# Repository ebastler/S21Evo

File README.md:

# S21Evo
NOTE: This project is still WIP. An older revision is currently being prototyped and has served as a software development platform. The state published in this repository includes a variety of bugfixes and improvements over this version, but is as of now UNTESTED. The current firmware does not support these changes yet. Please do not order PCBs based off this repository (and if you do, don't complain about problems).

## Introduction
This project was born from the fact that the Convoy S21E is - in my opinion - one of the best budget flashlights out there. It is fairly compact for a 21700 class flashlight. 21700 batteries are a great compromise between size and capacity. It can fit a variety of emitters and optics. It is available in a lot of nice colors - and all that while being very affordable. I do, however, not like Convoys E-Switch drivers much due to some UI choices that do not reflect my preference. I also wanted faster charging and powerbank functionality included.

## Features
The S21Evo BST driver is a high-efficiency 6V 5A boost driver. It is based on the popular MPS MP3432 boost chip. Two shunts (1 Ohm and 7 mOhm) allow for a wide dynamic range (~100uA to 5A). The battery management (15W charging, 15W reverse powerbank functionality with proper USB-C handshake) is handled by a MPS MP2722. A STM32C072GBU controls both chips and can be programmed seamlessly via the built-in USB port of the flashlight. Thermal protection, low-voltage protection as well as reverse polarity protection are built in. RGB Aux (2 brightness levels per color) is available.

Some features I wanted to add (buck-boost supply for the MCU to allow for wider input voltage range, full 8bit RGB Aux, a MCU with built-in DAC instead of low-pass-filtered PWM) sadly had to be omitted due to severe space constraints in the S21E body. Fitting a USB-C port, battery spring, 2 DC-DC converters (15W and 30W) with as much filter capacity as possible as well as a QFN MCU in the given space was already a difficult task.

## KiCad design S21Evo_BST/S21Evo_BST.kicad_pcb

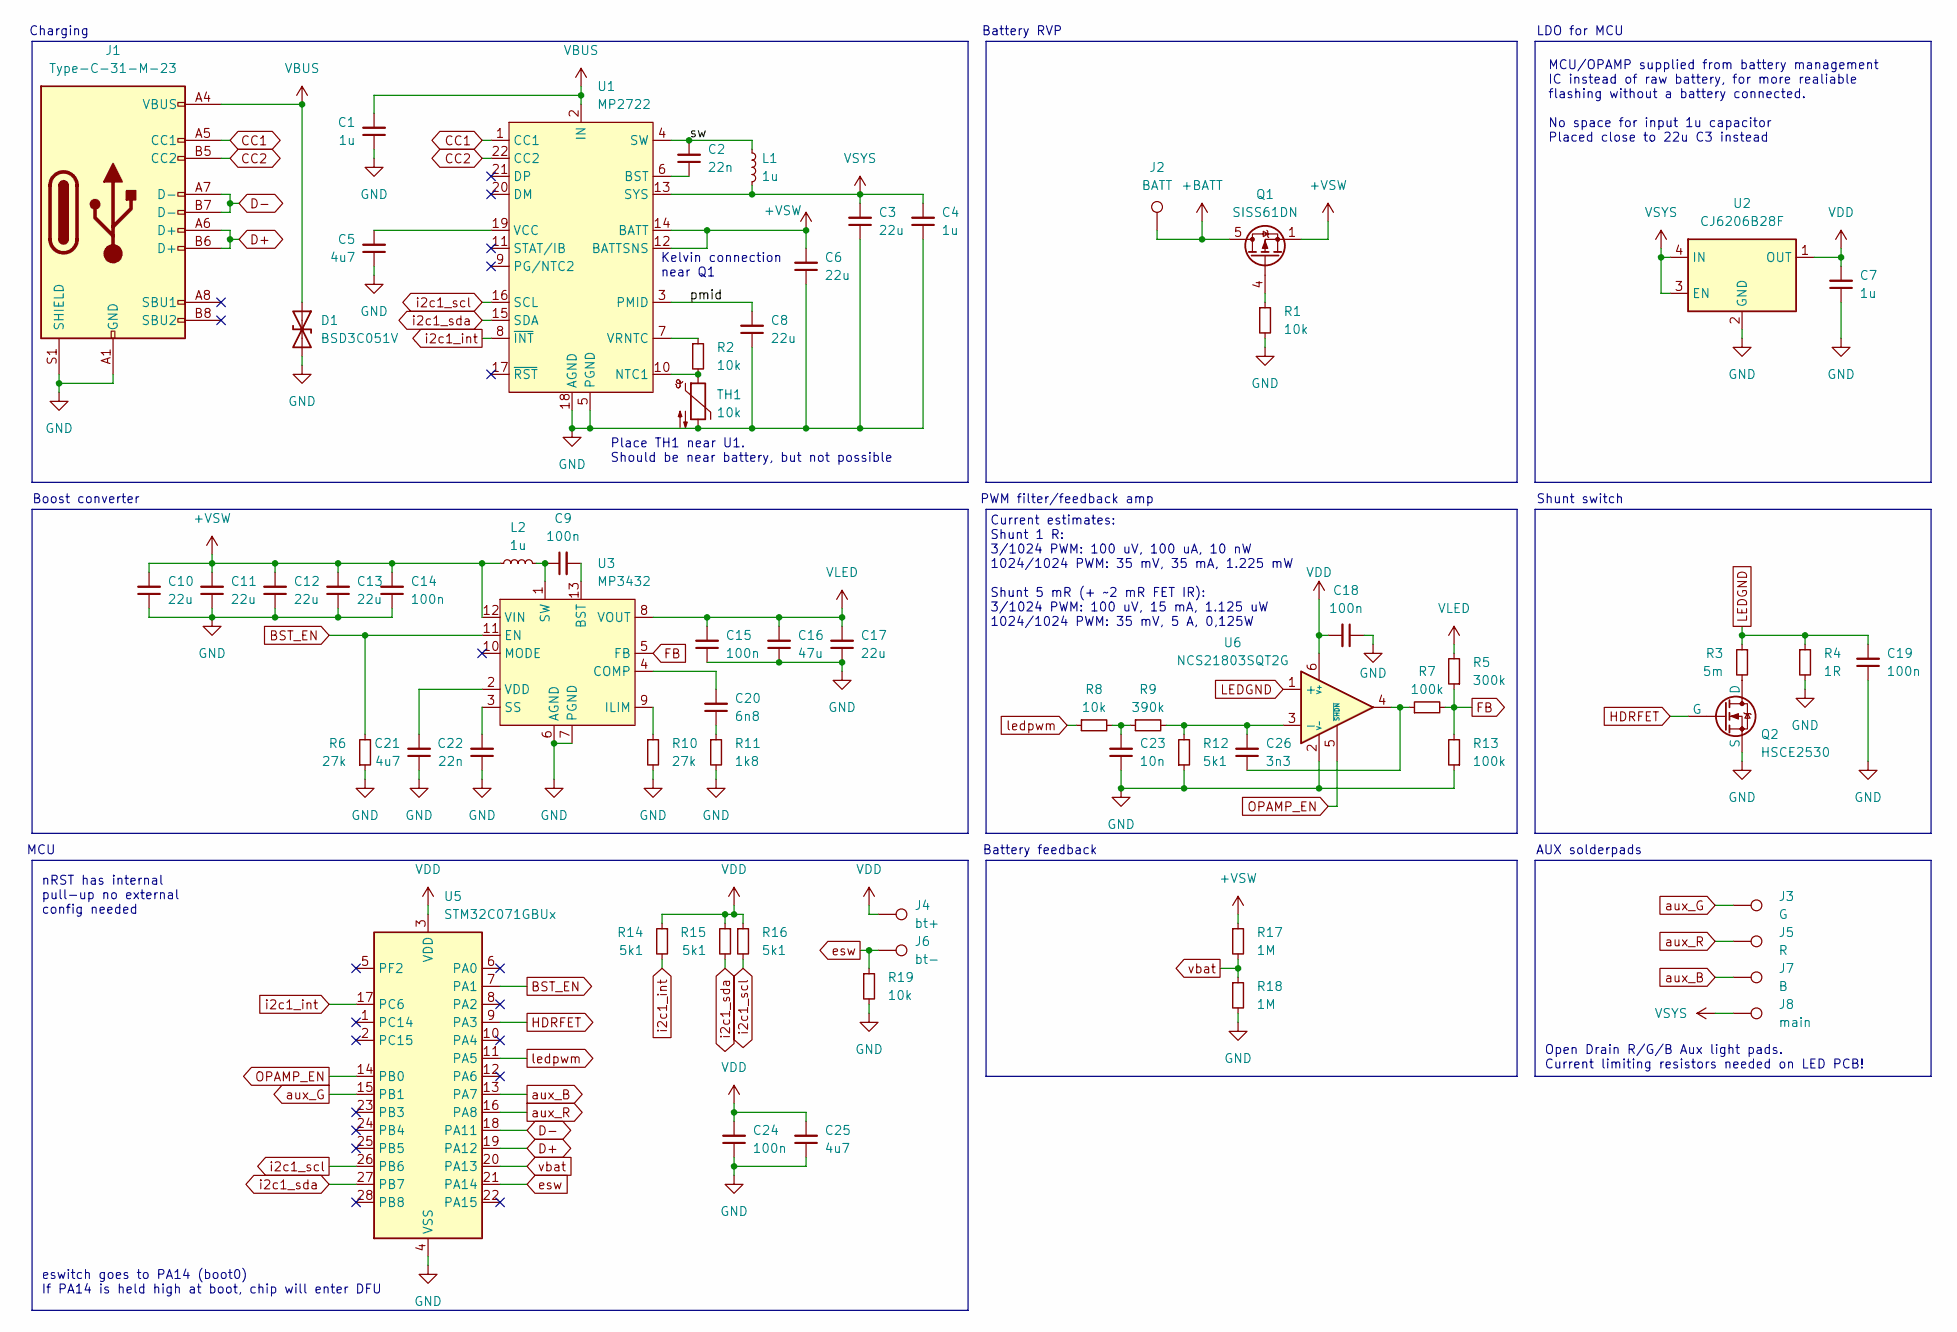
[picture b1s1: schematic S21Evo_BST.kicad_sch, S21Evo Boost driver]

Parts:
C1, C4, C7: 1u; C_0402_1005Metric; Part number CL05A105KA5NQNC; LCSC C52923
C2, C22: 22n; C_0402_1005Metric; Part number CL05B223KA5NNNC; LCSC C318578
C3, C6, C8, C10, C11, C13, C17: 22u; C_0603_1608Metric; Part number CL10A226MO7JZNC; LCSC C2762594
C5, C21, C25: 4u7; C_0402_1005Metric; Part number CL05A475MP5NRNC; LCSC C23733
C9, C14, C15, C18, C19, C24: 100n; C_0402_1005Metric; Part number CL05B104KB54PNC; LCSC C307331
C12: 22u; C_0805_2012Metric; Part number CL21A226MAQNNNE; LCSC C45783
C16: 47u; C_1206_3216Metric; Part number CL31A476MPHNNNE; LCSC C96123
C20: 6n8; C_0402_1005Metric; Part number CL05B682KB5NNNC; LCSC C318580
C23: 10n; C_0402_1005Metric; Part number CL05B103KB5NNNC; LCSC C15195
C26: 3n3; C_0402_1005Metric; Part number CL05B332KB5NNNC; LCSC C26404
D1: BSD3C051V; D_SOD-323; Part number BSD3C051V; LCSC C151996
J1: Type-C-31-M-23; USB_C_Receptacle_HRO_TYPE-C-31-M-23; Part number TYPE-C-31-M-23; LCSC C530613
J2: BATT; spring_6mm
J3: G; auxpad
J4: bt+; auxpad
J5: R; auxpad
J6: bt-; auxpad
J7: B; auxpad
J8: main; auxpad
L1: 1u; L_Changjiang_FTC322520S; Part number YSMC322520H-1R0MB; LCSC C46962057
L2: 1u; L_Bourns_SRP6060FA; Part number YSPIT0660A-1R0M; LCSC C18199443
Q1: SISS61DN; Vishay_PowerPAK_1212-8_Single; Part number SISS61DN-T1-GE3; LCSC C3289430
Q2: HSCE2530; Vishay_PowerPAK_1212-8_Single; Part number HSCE2530; LCSC C701041
R1, R2, R8, R19: 10k; R_0402_1005Metric; Part number 0402WGF1002TCE; LCSC C25744
R3: 5m; R_0805_2012Metric; Part number MS05W2F500NT5E; LCSC C92742
R4: 1R; R_0402_1005Metric; Part number 0402WGF100KTCE; LCSC C25086
R5: 300k; R_0402_1005Metric; Part number 0402WGF3003TCE; LCSC C25774
R6, R10: 27k; R_0402_1005Metric; Part number 0402WGF2702TCE; LCSC C25771
R7, R13: 100k; R_0402_1005Metric; Part number 0402WGF1003TCE; LCSC C25741
R9: 390k; R_0402_1005Metric; Part number 0402WGF3903TCE; LCSC C25782
R11: 1k8; R_0402_1005Metric; Part number 0402WGF1801TCE; LCSC C25871
R12, R14, R15, R16: 5k1; R_0402_1005Metric; Part number 0402WGF5101TCE; LCSC C25905
R17, R18: 1M; R_0402_1005Metric; Part number 0402WGF1004TCE; LCSC C26083
TH1: 10k; R_0402_1005Metric; Part number NTCG103JF103FT1; LCSC C209959
U1: MP2722; QFN-22_MP2722_2.5x3.5mm_P0.4mm; Part number MP2722GRH-0000-Z; LCSC C20099551
U2: CJ6206B28F; OnSemi_XDFN4-1EP_1.0x1.0mm_EP0.52x0.52mm; Part number CJ6206B28F; LCSC C2829371
U3: MP3432; QFN-13_3x4mm_P0.5mm; Part number MP3432GL-Z; LCSC C3187976
U5: STM32C071GBUx; QFN-28_4x4mm_P0.5mm; Part number STM32C071GBU6; LCSC C42113261
U6: NCS21803SQT2G; SOT-363_SC-70-6; Part number NCS21803SQT2G; LCSC C5209288

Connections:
+BATT: J2.1 (1_1), Q1.5 (D)
+VSW: C6.2, C10.2, C11.2, C12.2, C13.2, C14.2, L2.1, Q1.1 (S), Q1.2 (S), Q1.3 (S), R17.1, U1.12 (BATTSNS), U1.14 (BATT), U3.12 (VIN)
/pmid: C8.2, U1.3 (PMID)
/sw: C2.2, L1.1, U1.4 (SW)
BST_EN: R6.2, U3.11 (EN), U5.7 (PA1)
CC1: J1.A5 (CC1), U1.1 (CC1)
CC2: J1.B5 (CC2), U1.22 (CC2)
D+: J1.A6 (D+), J1.B6 (D+), U5.19 (PA12)
D-: J1.A7 (D-), J1.B7 (D-), U5.18 (PA11)
FB: R5.1, R7.2, R13.2, U3.5 (FB)
GND: C1.1, C3.1, C4.1, C5.1, C6.1, C7.1, C8.1, C10.1, C11.1, C12.1, C13.1, C14.1, C15.1, C16.1, C17.1, C18.1, C19.1, C21.1, C22.1, C23.1, C24.1, C25.1, D1.2 (A2), J1.A1 (GND), J1.A12 (GND), J1.B1 (GND), J1.B12 (GND), J1.S1 (SHIELD), Q2.1 (S), Q2.2 (S), Q2.3 (S), R1.2, R4.2, R6.1, R10.2, R11.2, R12.1, R13.1, R18.2, R19.2, TH1.2, U1.5 (PGND), U1.18 (AGND), U2.2 (GND), U2.5 (GND), U3.6 (AGND), U3.7 (PGND), U5.4 (VSS), U6.2 (V-)
HDRFET: Q2.4 (G), U5.9 (PA3)
LEDGND: C19.2, R3.1, R4.1, U6.1 (+)
unnamed: C20.1, R11.1
unnamed: C23.2, R8.2, R9.1
unnamed: C26.1, R7.1, U6.4
unnamed: Q1.4 (G), R1.1
unnamed: Q2.5 (D), Q2.6 (D), Q2.7 (D), Q2.8 (D), Q2.9 (D), R3.2
unnamed: C2.1, U1.6 (BST)
unnamed: R2.2, TH1.1, U1.10 (NTC1)
unnamed: C5.2, U1.19 (VCC)
unnamed: R2.1, U1.7 (VRNTC)
unnamed: C9.2, U3.13 (BST)
unnamed: C20.2, U3.4 (COMP)
unnamed: R10.1, U3.9 (ILIM)
unnamed: C22.2, U3.3 (SS)
unnamed: C9.1, L2.2, U3.1 (SW)
unnamed: C21.2, U3.2 (VDD)
unnamed: C26.2, R9.2, R12.2, U6.3 (-)
OPAMP_EN: U5.14 (PB0), U6.5 (~SHDN)
VBUS: C1.2, D1.1 (A1), J1.A4 (VBUS), J1.A9 (VBUS), J1.B4 (VBUS), J1.B9 (VBUS), U1.2 (IN)
VDD: C7.2, C18.2, C24.2, C25.2, J4.1 (1_1), R14.1, R15.1, R16.1, U2.1 (OUT), U5.3 (VDD), U6.6 (V+)
VLED: C15.2, C16.2, C17.2, R5.2, U3.8 (VOUT)
VSYS: C3.2, C4.2, J8.1 (1_1), L1.2, U1.13 (SYS), U2.3 (EN), U2.4 (IN)
aux_B: J7.1 (1_1), U5.13 (PA7)
aux_G: J3.1 (1_1), U5.15 (PB1)
aux_R: J5.1 (1_1), U5.16 (PA8)
esw: J6.1 (1_1), R19.1, U5.21 (PA14)
i2c1_int: R14.2, U1.8 (~INT), U5.17 (PC6)
i2c1_scl: R16.2, U1.16 (SCL), U5.26 (PB6)
i2c1_sda: R15.2, U1.15 (SDA), U5.27 (PB7)
ledpwm: R8.1, U5.11 (PA5)
vbat: R17.2, R18.1, U5.20 (PA13)

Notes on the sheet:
eswitch goes to PA14 (boot0) If PA14 is held high at boot, chip will enter DFU
nRST has internal pull-up no external config needed
Place TH1 near U1. Should be near battery, but not possible
MCU/OPAMP supplied from battery management IC instead of raw battery, for more realiable flashing without a battery connected. No space for input 1u capacitor Placed close to 22u C3 instead
LDO for MCU
Battery feedback
PWM filter/feedback amp
Battery RVP
Shunt switch
Current estimates: Shunt 1 R: 3/1024 PWM: 100 uV, 100 uA, 10 nW 1024/1024 PWM: 35 mV, 35 mA, 1.225 mW Shunt 5 mR (+ ~2 mR FET IR): 3/1024 PWM: 100 uV, 15 mA, 1.125 uW 1024/1024 PWM: 35 mV, 5 A, 0,125W
Charging
MCU
AUX solderpads
Boost converter
Open Drain R/G/B Aux light pads. Current limiting resistors needed on LED PCB!
Kelvin connection near Q1

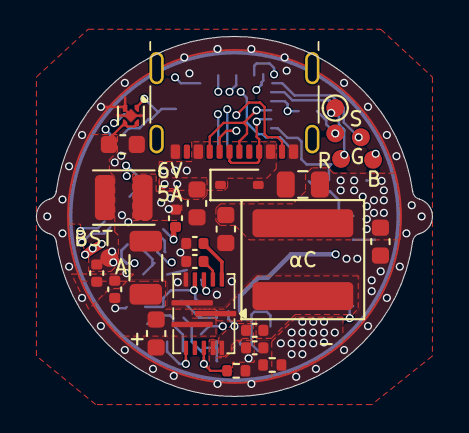
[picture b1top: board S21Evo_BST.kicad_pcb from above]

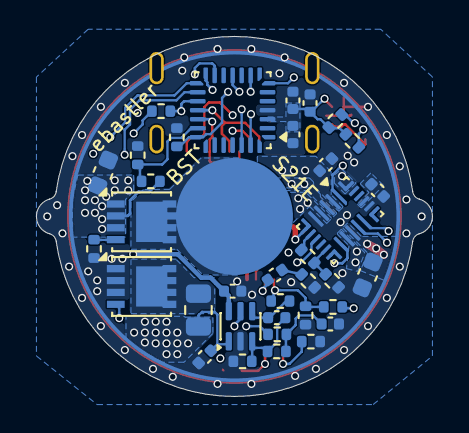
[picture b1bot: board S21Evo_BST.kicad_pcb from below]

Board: 4 copper layers, 22.0 x 20.0 mm, 64 parts (36 on the bottom side), 43 nets.

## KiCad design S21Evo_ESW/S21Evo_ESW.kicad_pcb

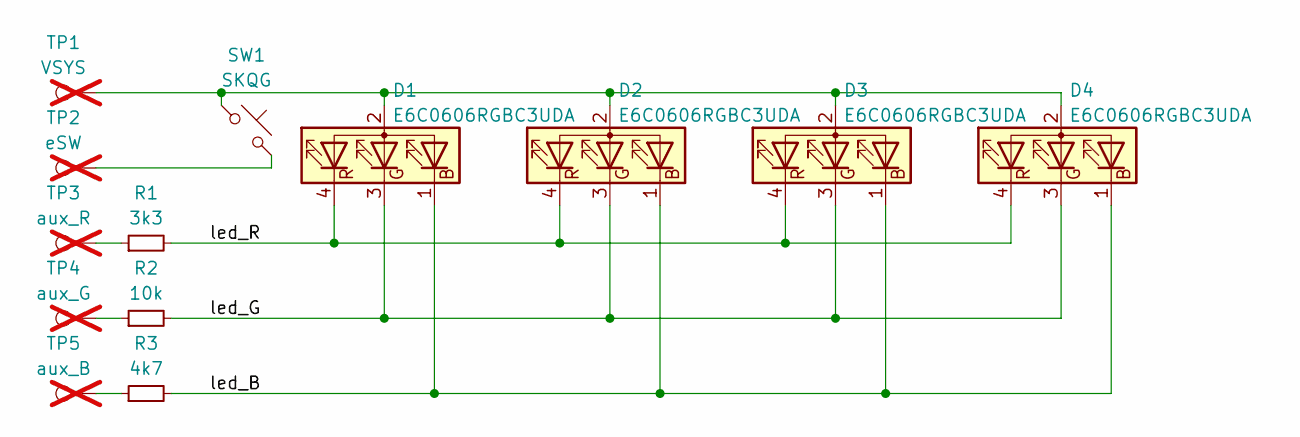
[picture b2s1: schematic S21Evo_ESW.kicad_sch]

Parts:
D1, D2, D3, D4: E6C0606RGBC3UDA; LED_1616; Part number E6C0606RGBC3UDA; LCSC C375569
R1: 3k3; R_0402_1005Metric; Part number 0402WGF3301TCE; LCSC C25890
R2: 10k; R_0402_1005Metric; Part number 0402WGF1002TCE; LCSC C25744
R3: 4k7; R_0402_1005Metric; Part number 0402WGF4701TCE; LCSC C25900
SW1: SKQG; SW_SPST_SKQG_WithStem; Part number SKQGABE010; LCSC C115351
TP1: VSYS; auxpad; not fitted
TP2: eSW; auxpad; not fitted
TP3: aux_R; auxpad; not fitted
TP4: aux_G; auxpad; not fitted
TP5: aux_B; auxpad; not fitted

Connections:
/led_B: D1.1 (BK), D2.1 (BK), D3.1 (BK), D4.1 (BK), R3.2
/led_G: D1.3 (GK), D2.3 (GK), D3.3 (GK), D4.3 (GK), R2.2
/led_R: D1.4 (RK), D2.4 (RK), D3.4 (RK), D4.4 (RK), R1.2
unnamed: D1.2 (A), D2.2 (A), D3.2 (A), D4.2 (A), SW1.1, TP1.1
unnamed: R1.1, TP3.1
unnamed: R2.1, TP4.1
unnamed: R3.1, TP5.1
unnamed: SW1.2, TP2.1

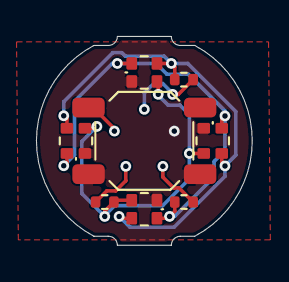
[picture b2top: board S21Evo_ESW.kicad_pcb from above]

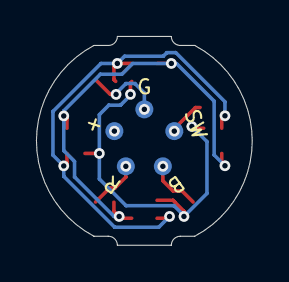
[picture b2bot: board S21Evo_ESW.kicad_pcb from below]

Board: 2 copper layers, 12.0 x 11.6 mm, 13 parts (5 on the bottom side), 8 nets.
